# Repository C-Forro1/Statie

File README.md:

# Statie: A Desk Status Light!
A modified version of the 'Starbie' Project (cc: SharKingStudios) for marking the status of your desk so your pesky children don't bother you!

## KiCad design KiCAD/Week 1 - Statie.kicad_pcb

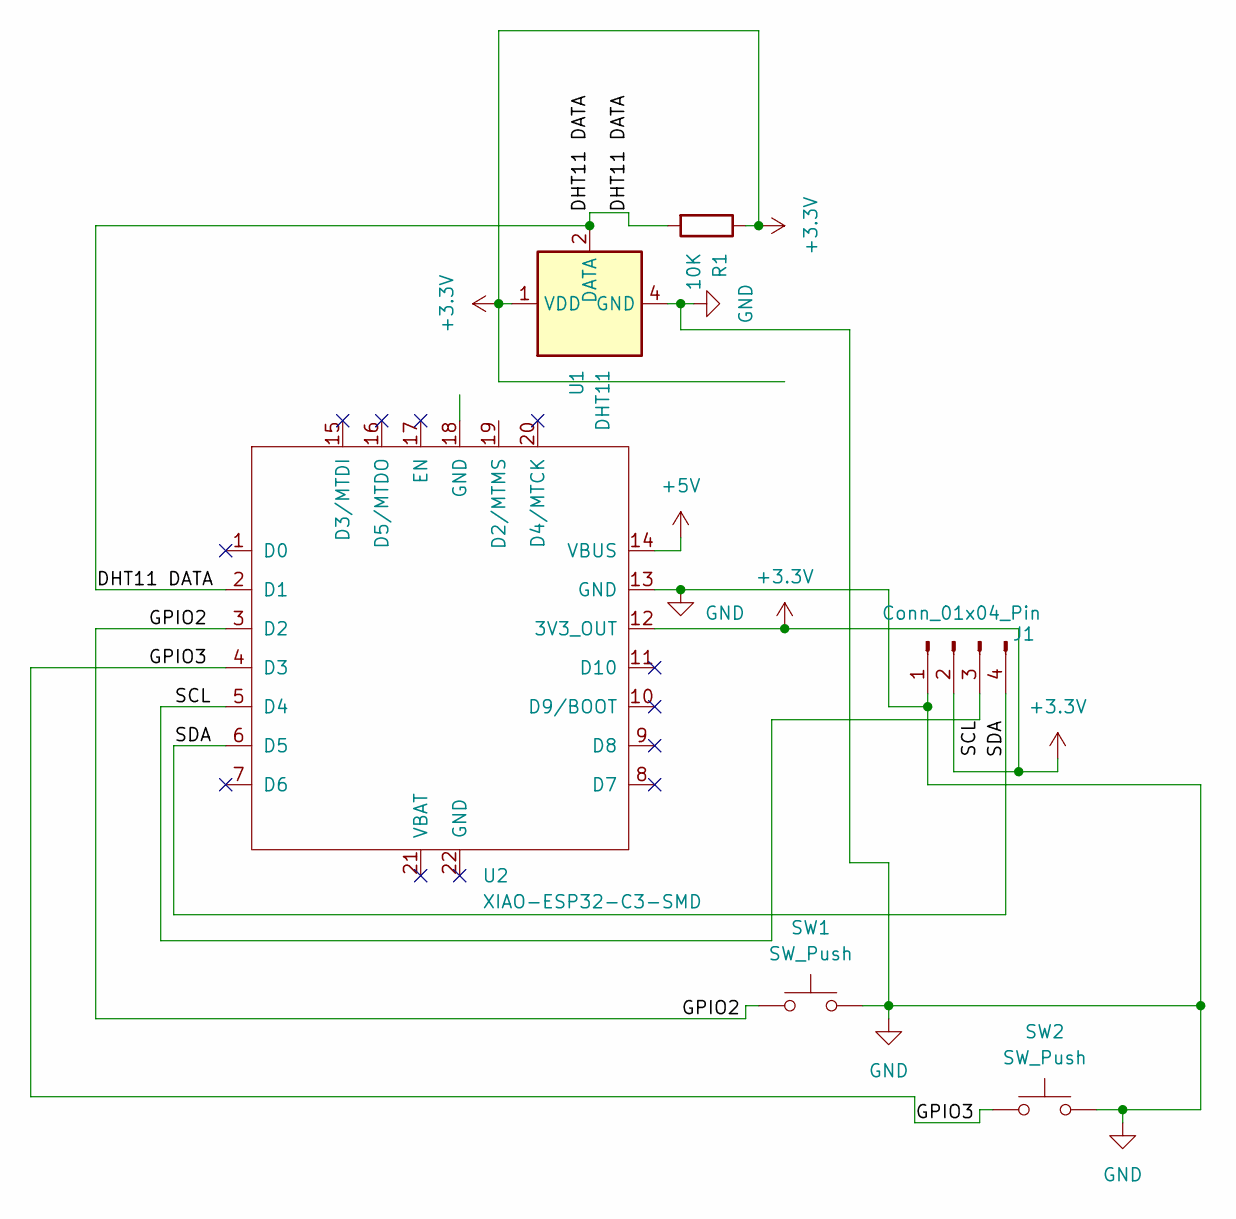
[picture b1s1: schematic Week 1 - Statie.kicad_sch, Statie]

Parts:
J1: Conn_01x04_Pin; Display_128x64_096_I2C
R1: 10K; R_Axial_DIN0204_L3.6mm_D1.6mm_P7.62mm_Horizontal
SW1, SW2: SW_Push; SW_Cherry_MX_1.00u_PCB
U1: DHT11; Aosong_DHT11_5.5x12.0_P2.54mm
U2: XIAO-ESP32-C3-SMD; XIAO-ESP32-C3-DIP-SMD

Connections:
+3.3V: J1.2, R1.1, U1.1 (VDD), U2.12 (3V3_OUT)
+5V: U2.14 (VBUS)
/DHT11 DATA: R1.2, U1.2 (DATA), U2.2 (D1)
/GPIO2: SW1.1, U2.3 (D2)
/GPIO3: SW2.1, U2.4 (D3)
/SCL: J1.3, U2.5 (D4)
/SDA: J1.4, U2.6 (D5)
GND: J1.1, SW1.2, SW2.2, U1.4 (GND), U2.13 (GND)

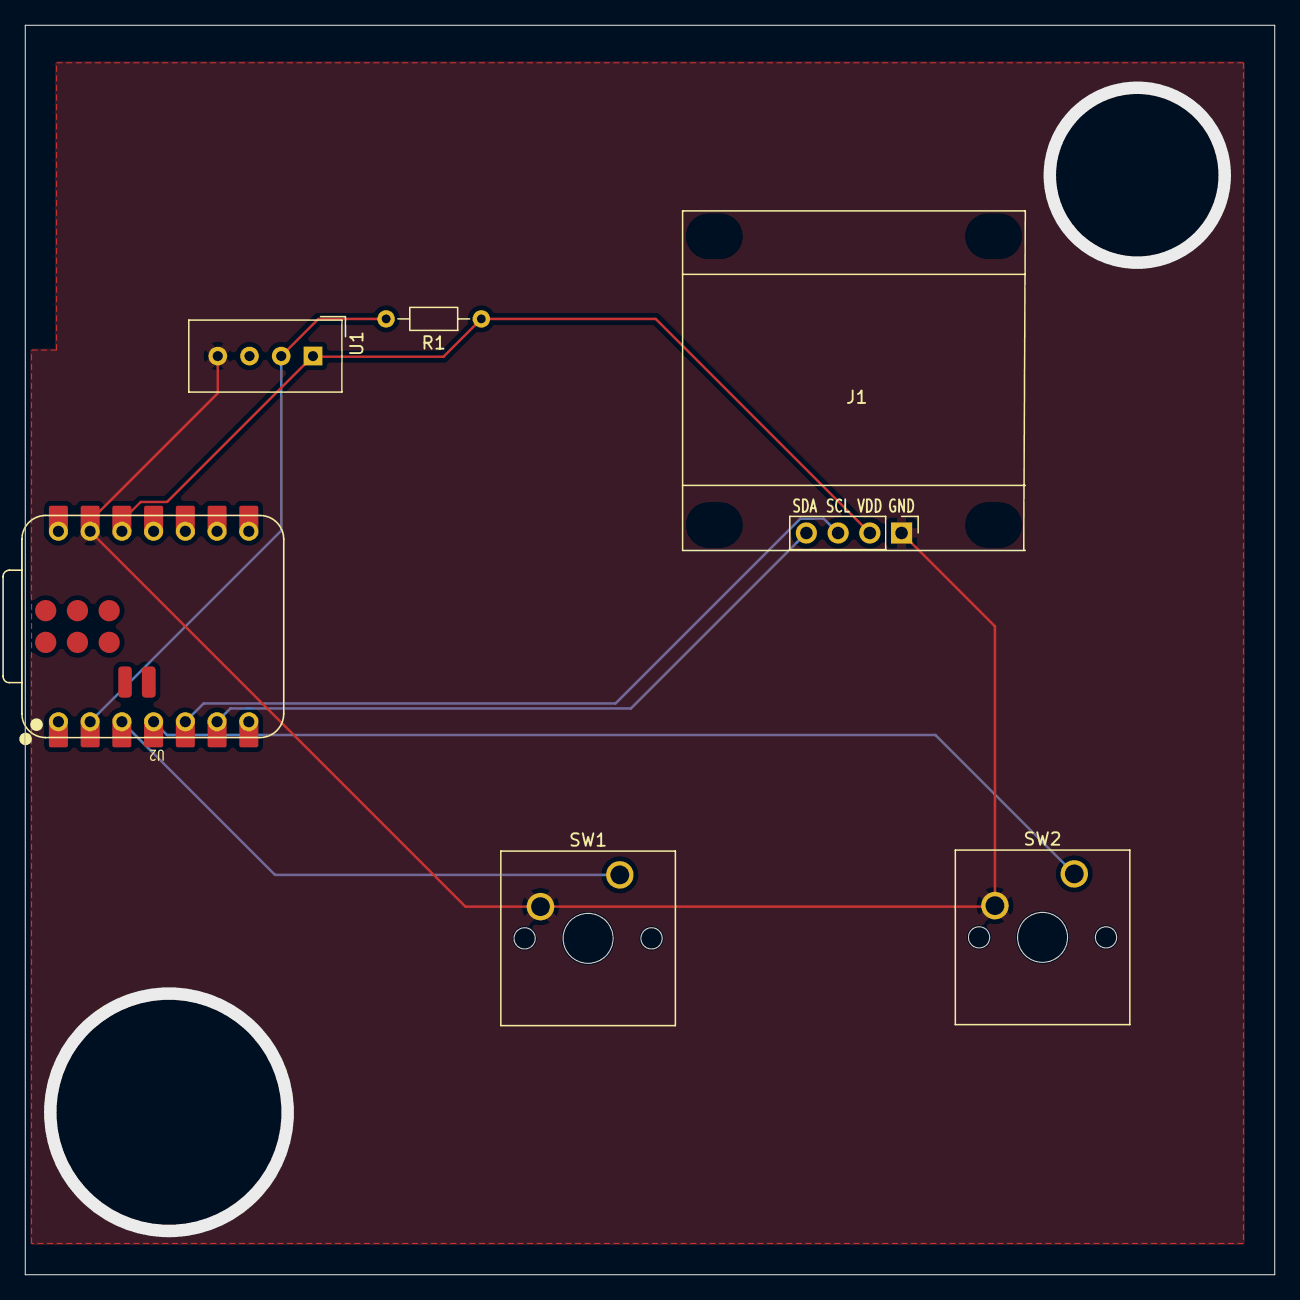
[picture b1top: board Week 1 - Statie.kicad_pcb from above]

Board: 2 copper layers, 100.0 x 100.0 mm, 6 parts (0 on the bottom side), 7 nets.
